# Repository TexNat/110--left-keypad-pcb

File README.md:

# 110% left keypad pcb
 pcb for a 110% keyboard with the keypad on the left

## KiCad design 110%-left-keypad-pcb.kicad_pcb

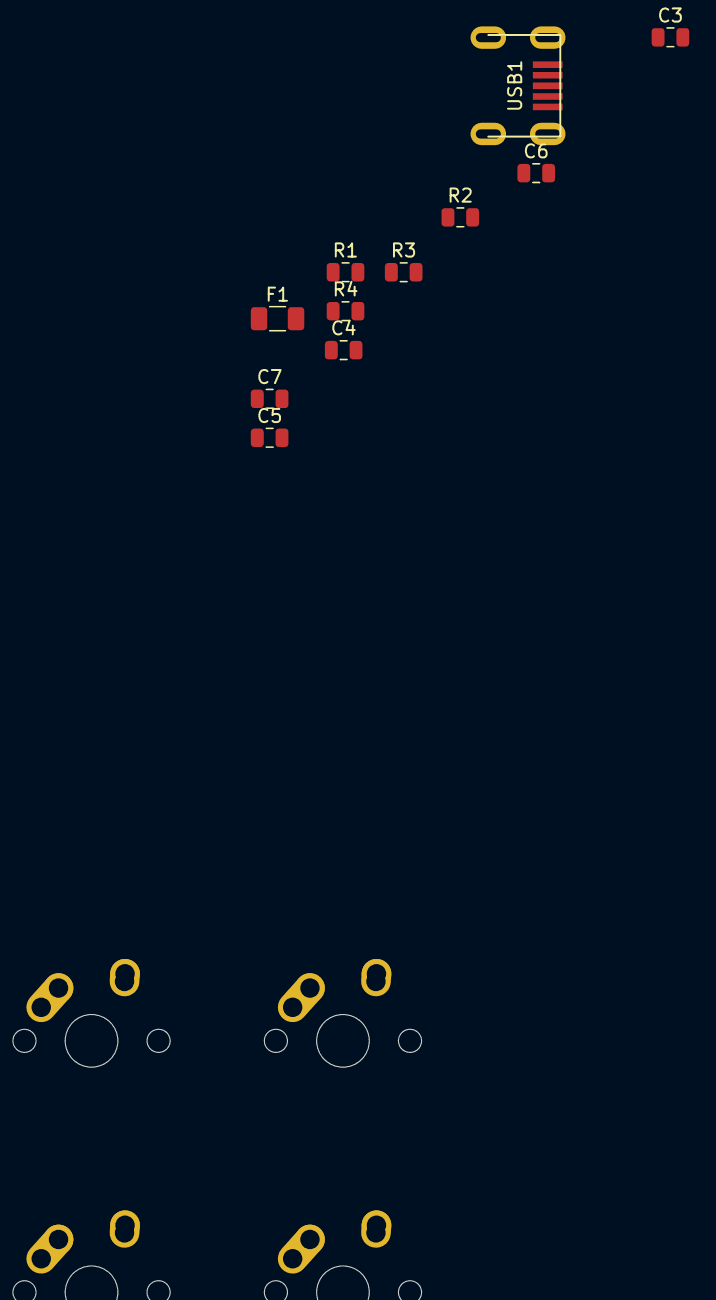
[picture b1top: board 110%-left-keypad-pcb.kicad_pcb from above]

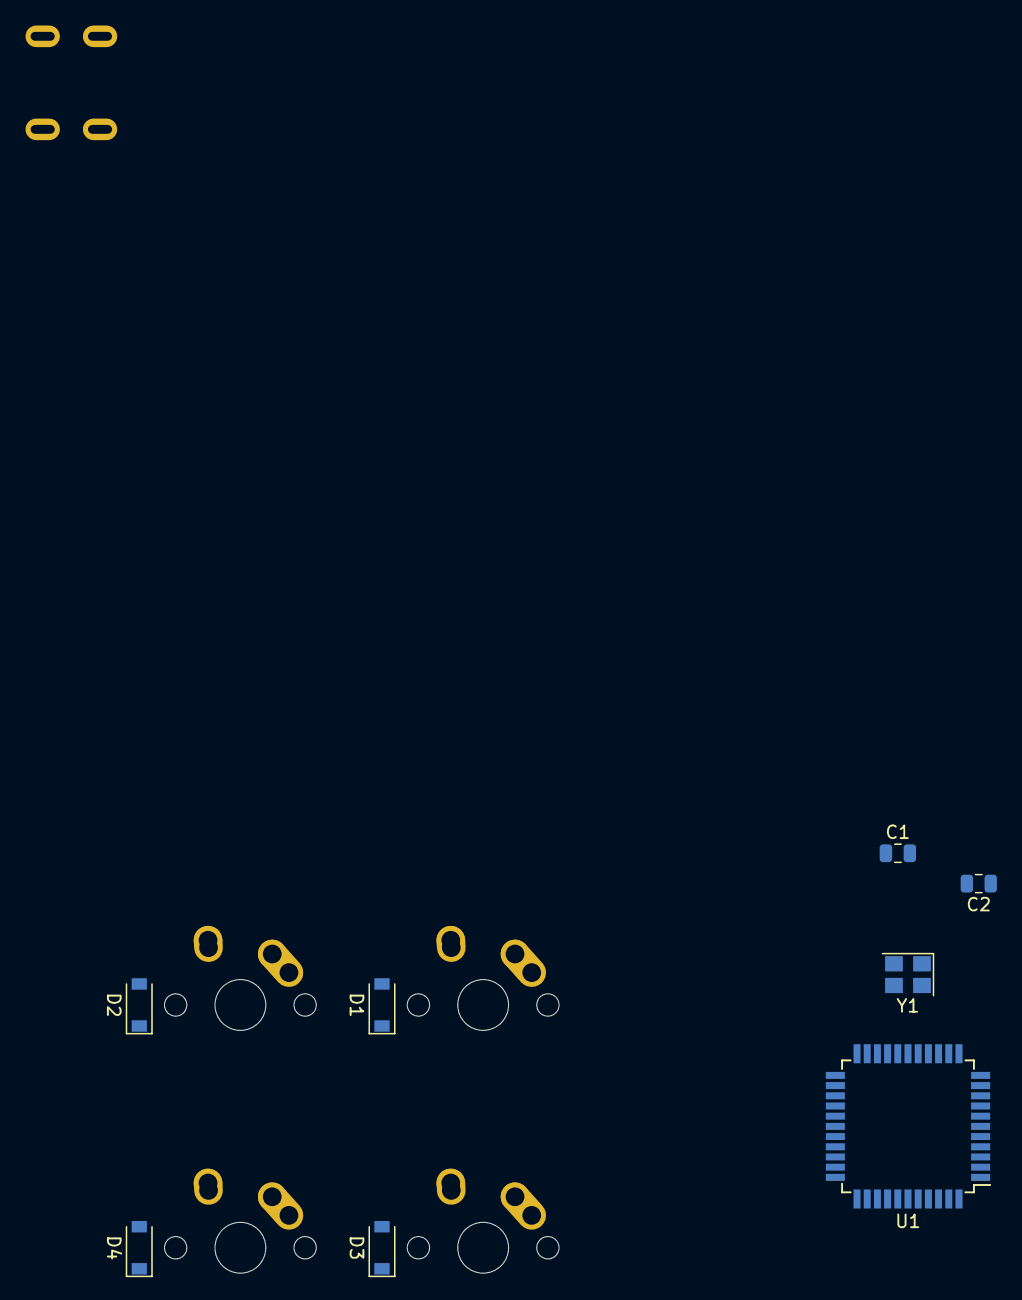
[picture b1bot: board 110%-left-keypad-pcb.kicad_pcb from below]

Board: 2 copper layers, 23 parts (8 on the bottom side), 20 nets, no tracks yet.

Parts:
C1, C2: 22pF; C_0805_2012Metric
C3: 1uF; C_0805_2012Metric
C4, C5, C6: 0.1uF; C_0805_2012Metric
C7: 10uF; C_0805_2012Metric
D1, D2, D3, D4: SOD-123; D_SOD-123
F1: Polyfuse_Small; Fuse_1206_3216Metric
MX1, MX2, MX3, MX4: MX-NoLED; MX-1U-NoLED
R1, R4: 10k; R_0805_2012Metric
R2, R3: 22; R_0805_2012Metric
U1: ATmega32U4-AU; TQFP-44_10x10mm_P0.8mm
USB1: Molex-0548190589
Y1: 16MHz; Crystal_SMD_3225-4Pin_3.2x2.5mm

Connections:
+5V: C4.1, C5.1, C6.1, C7.1, F1.1, R1.1, U1.2, U1.7, U1.14, U1.24, U1.34, U1.44
COL0: MX1.1, MX3.1
COL1: MX2.1, MX4.1
D+: R2.2, USB1.3
D-: R3.2, USB1.4
GND: C1.2, C2.2, C3.2, C4.2, C5.2, C6.2, C7.2, R4.1, U1.5, U1.15, U1.23, U1.35, U1.43, USB1.1, Y1.2, Y1.4
unnamed: C1.1, U1.17, Y1.1
unnamed: C2.1, U1.16, Y1.3
unnamed: C3.1, U1.6
unnamed: D1.2, MX1.2
unnamed: D2.2, MX2.2
unnamed: D3.2, MX3.2
unnamed: D4.2, MX4.2
unnamed: R1.2, U1.13
unnamed: R2.1, U1.4
unnamed: R3.1, U1.3
unnamed: R4.2, U1.33
ROW0: D1.1, D2.1
ROW1: D3.1, D4.1
VCC: F1.2, USB1.5

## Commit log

2023-03-12 create files
2023-03-12 add submodules
2023-03-12 assign symbol libraries
2023-03-12 complete schematic
2023-03-12 start work on pcb
